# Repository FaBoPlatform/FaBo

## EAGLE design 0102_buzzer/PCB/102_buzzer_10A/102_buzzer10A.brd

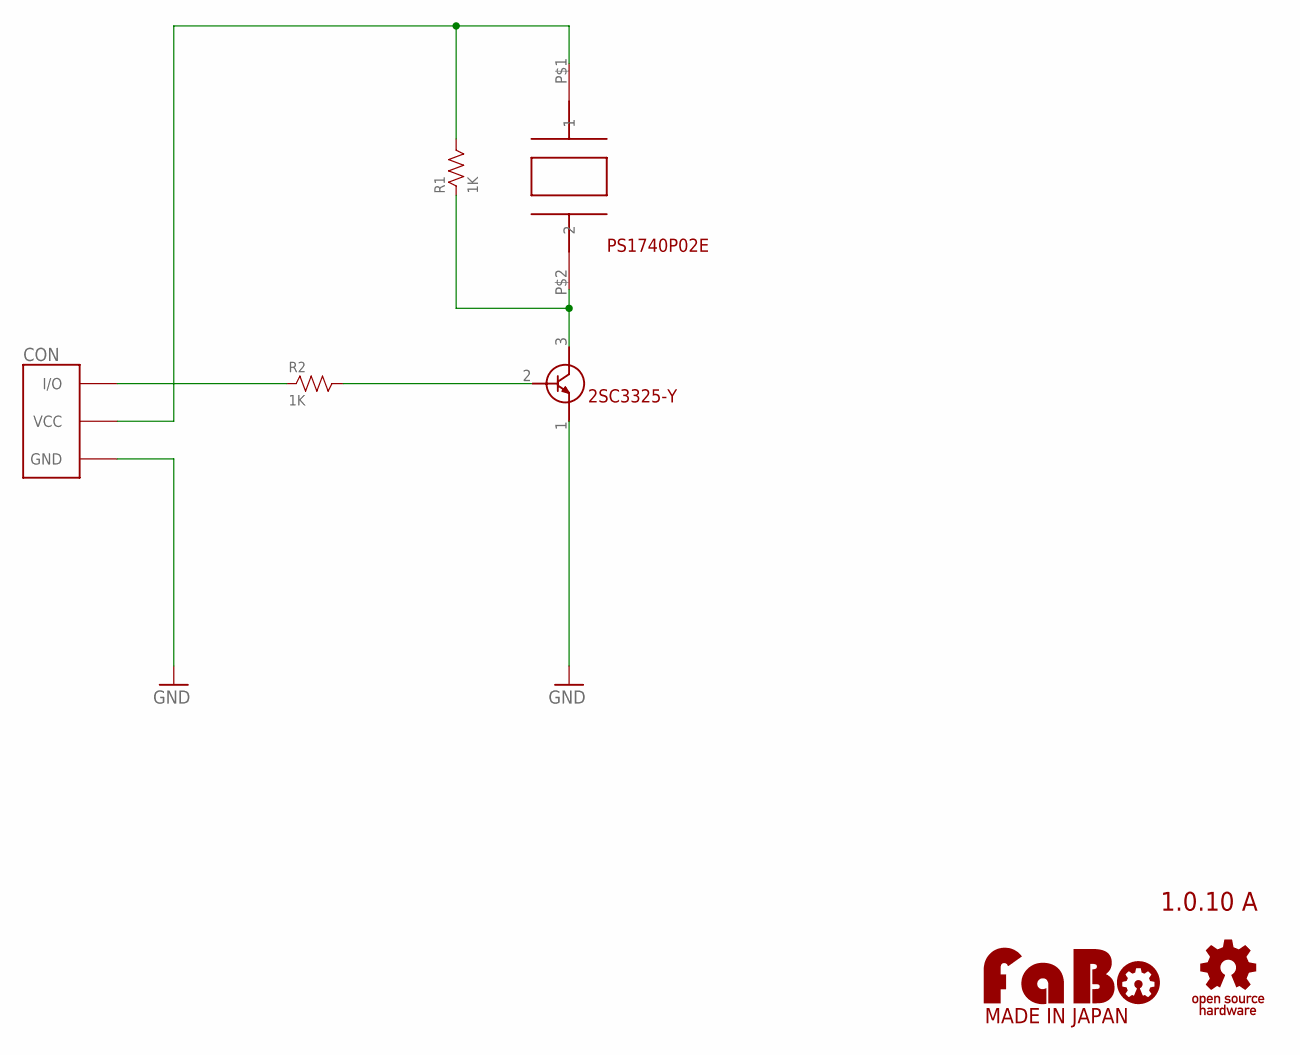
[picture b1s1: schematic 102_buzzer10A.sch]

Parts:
CON: FABO_BRICK_3PIN_INNER; FABO_BRICK_3PIN_HOLE_CON
R1, R2: 1K; 0603
T1: 2SC3325-Y; SC-59
U1: PS1740P02E
U$2: LOGO_FABO-M; LOGO_FABO_MS
U$3: LOGO_OSHW-M_BOTTOM; LOGO_OSHW_M_BOTTOM

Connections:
GND: CON.GND, T1.1 (E)
unnamed: CON.I/O, R2.1
unnamed: CON.VCC, R1.2, U1.P$1 (1)
unnamed: R1.1, T1.3 (C), U1.P$2 (2)
unnamed: R2.2, T1.2 (B)

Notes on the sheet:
1.0.10 A
PS1740P02E

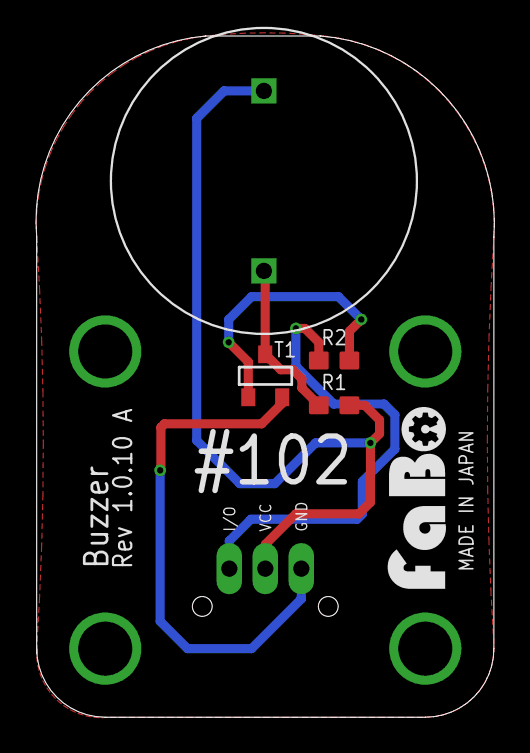
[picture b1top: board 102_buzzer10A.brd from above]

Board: 2 copper layers, 25.5 x 37.8 mm, 7 parts (0 on the bottom side), 5 nets.

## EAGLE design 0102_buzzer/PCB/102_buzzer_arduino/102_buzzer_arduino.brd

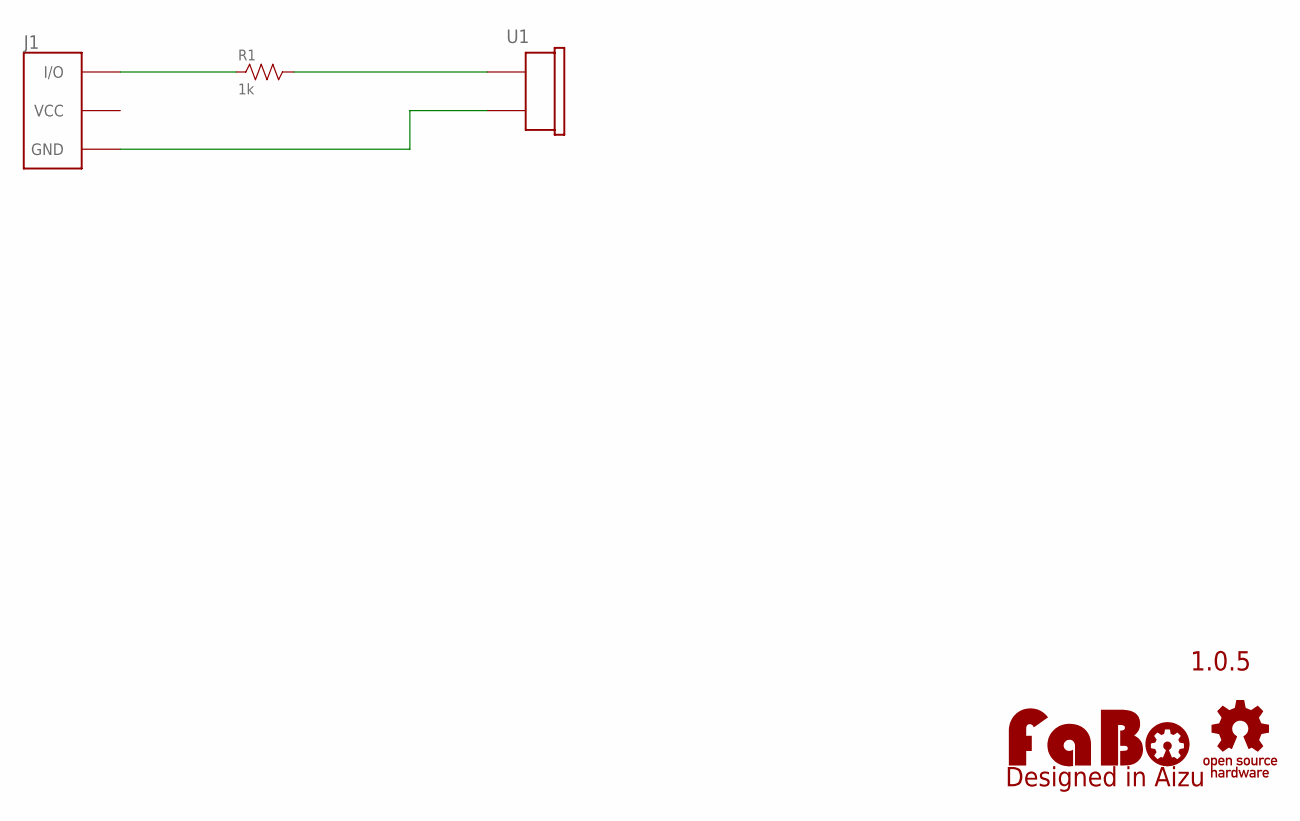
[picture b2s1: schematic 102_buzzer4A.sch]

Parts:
J1: FABO_BRICK_3PIN
LOGO1: LOGO_FABO-M; LOGO_FABO_M
R1: 1k; AXL-REGULAR
U1: BUZZER; PKM13EPYH4000-A0
U$3: LOGO_OSHW-M_BOTTOM; LOGO_OSHW_M_BOTTOM

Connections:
GND: J1.GND, U1.2
unnamed: J1.I/O, R1.1
unnamed: R1.2, U1.1

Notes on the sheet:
1.0.5

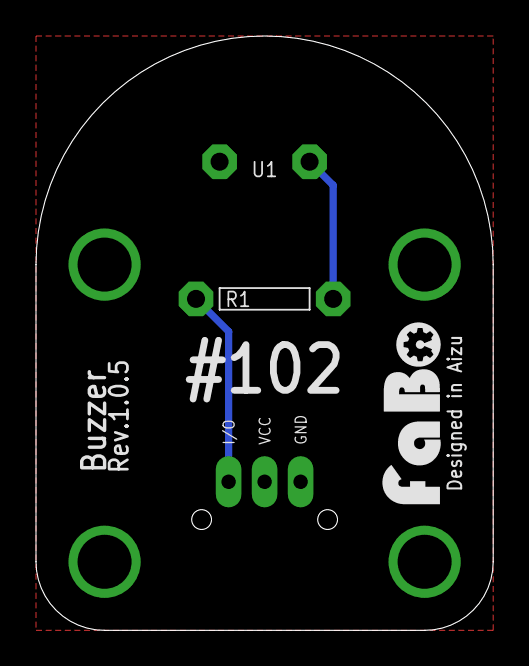
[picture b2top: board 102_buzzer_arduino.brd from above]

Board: 2 copper layers, 25.4 x 33.0 mm, 5 parts (0 on the bottom side), 3 nets.

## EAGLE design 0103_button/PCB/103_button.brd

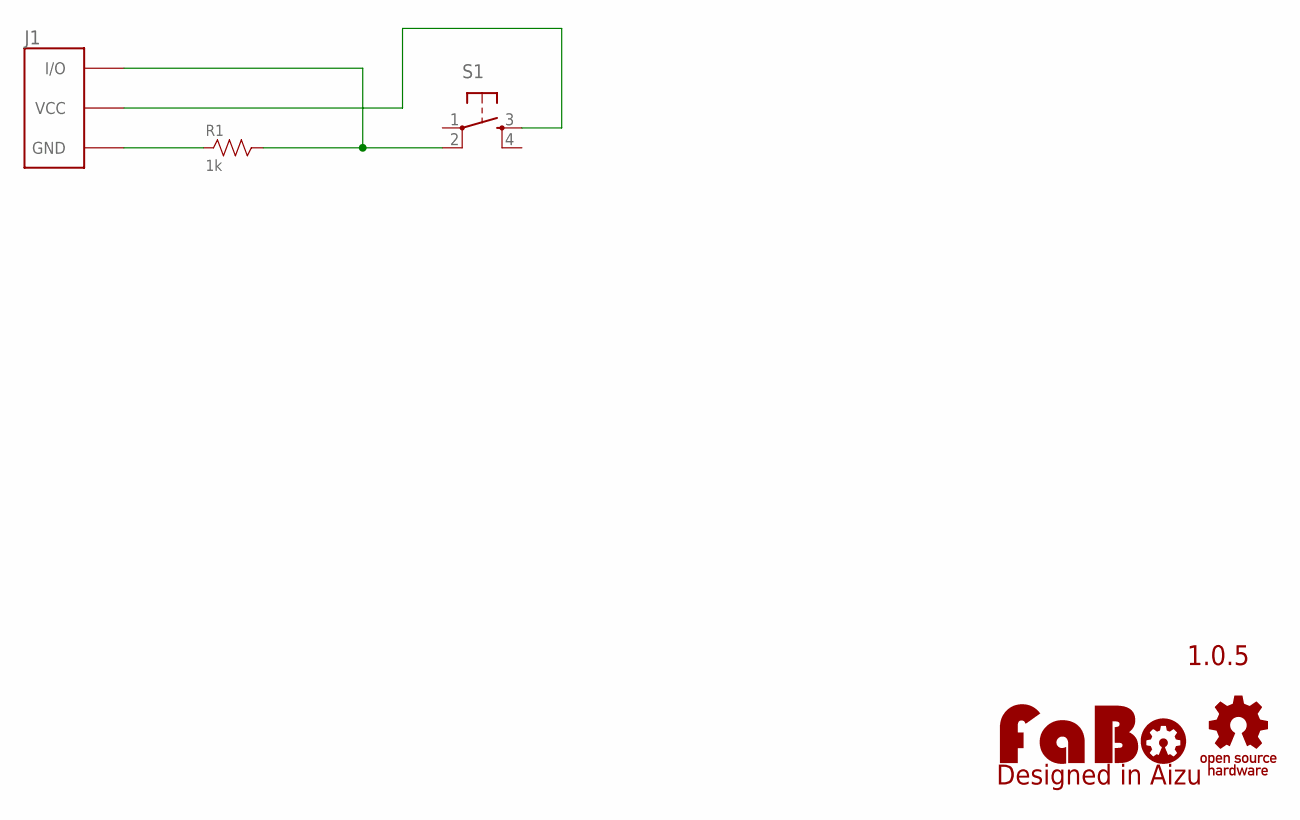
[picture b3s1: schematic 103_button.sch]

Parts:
J1: FABO_BRICK_3PIN
LOGO1: LOGO_FABO-M_BOTTOM; LOGO_FABO_M_BOTTOM
R1: 1k; AXL-REGULAR
S1: TACT-SWITCH-12MM; 1273HA-160G-G
U$2: LOGO_OSHW-M_BOTTOM; LOGO_OSHW_M_BOTTOM

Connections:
GND: J1.GND, R1.1
unnamed: J1.VCC, S1.3
unnamed: J1.I/O, R1.2, S1.2

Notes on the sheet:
1.0.5

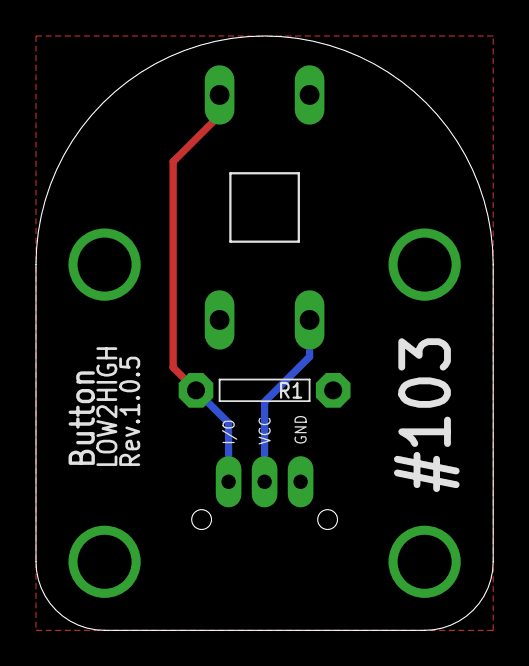
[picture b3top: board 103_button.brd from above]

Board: 2 copper layers, 25.4 x 33.0 mm, 5 parts (0 on the bottom side), 3 nets.

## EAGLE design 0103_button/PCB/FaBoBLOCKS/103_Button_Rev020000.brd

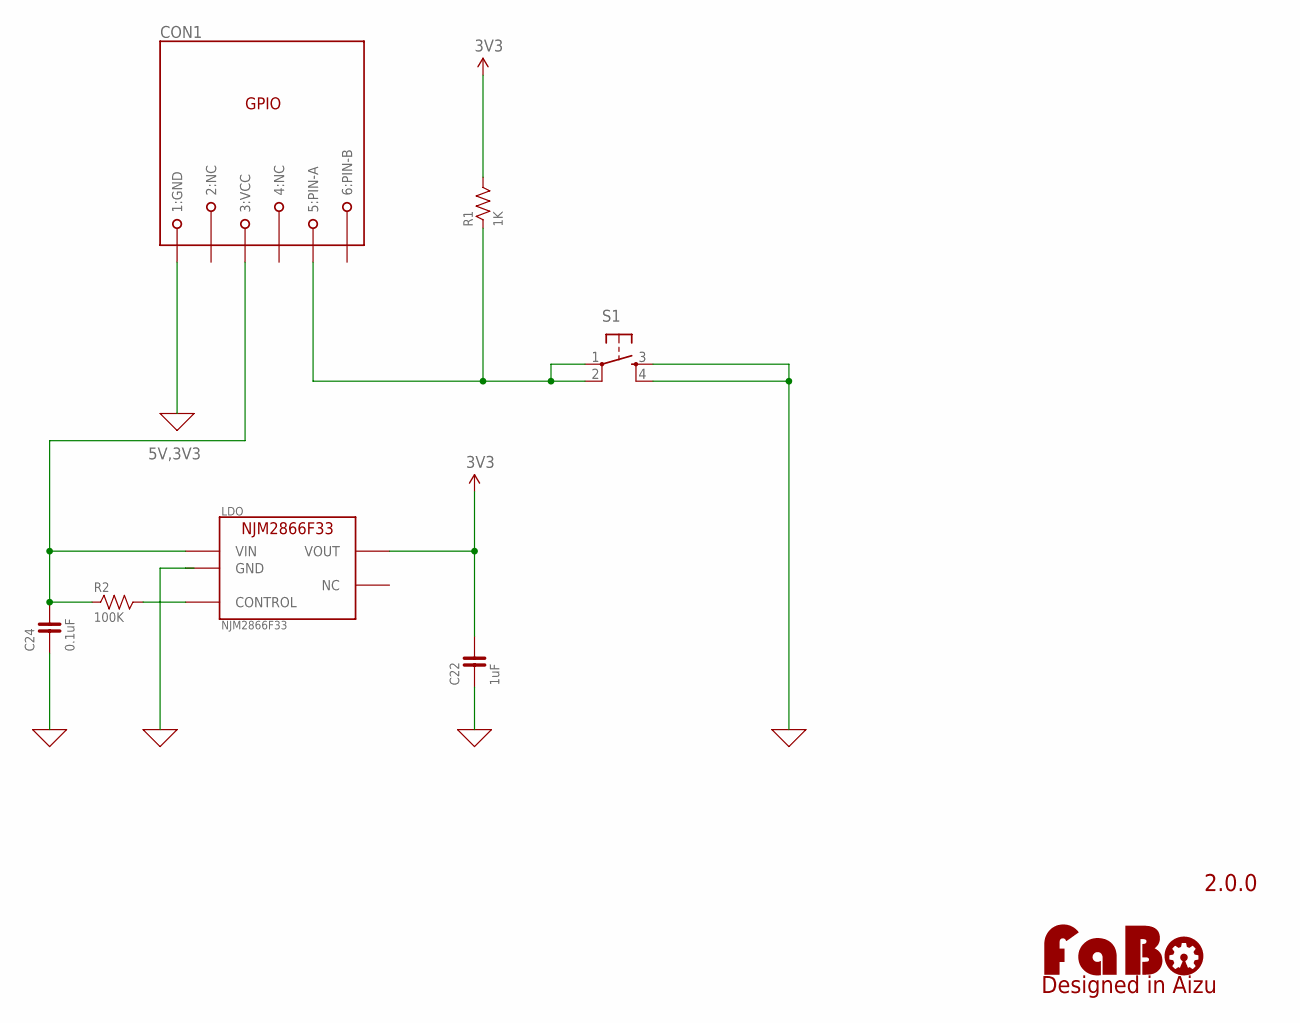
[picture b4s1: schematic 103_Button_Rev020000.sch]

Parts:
C22: 1uF; 0603
C24: 0.1uF; 0603
CON1: MODULAR-JACK-6P-RJ11_GPIO; 7002-6PXC-X
LDO: NJM2866F33; SOT-23-5
LOGO1: LOGO_FABO-M_BOTTOM; LOGO_FABO_M_BOTTOM
R1: 1K; 0603
R2: 100K; 0603
S1: TACT-SWITCH-12MM; 1273HA-160G-G

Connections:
0: C22.1, C24.1, CON1.1 (1:GND), LDO.2 (GND), S1.3, S1.4
3V3: C22.2, LDO.5 (VOUT), R1.2
5V,3V3: C24.2, CON1.3 (3:VCC), LDO.1 (VIN), R2.1
unnamed: CON1.5 (5:PIN-A), R1.1, S1.1, S1.2
unnamed: LDO.3 (CONTROL), R2.2

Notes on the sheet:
2.0.0

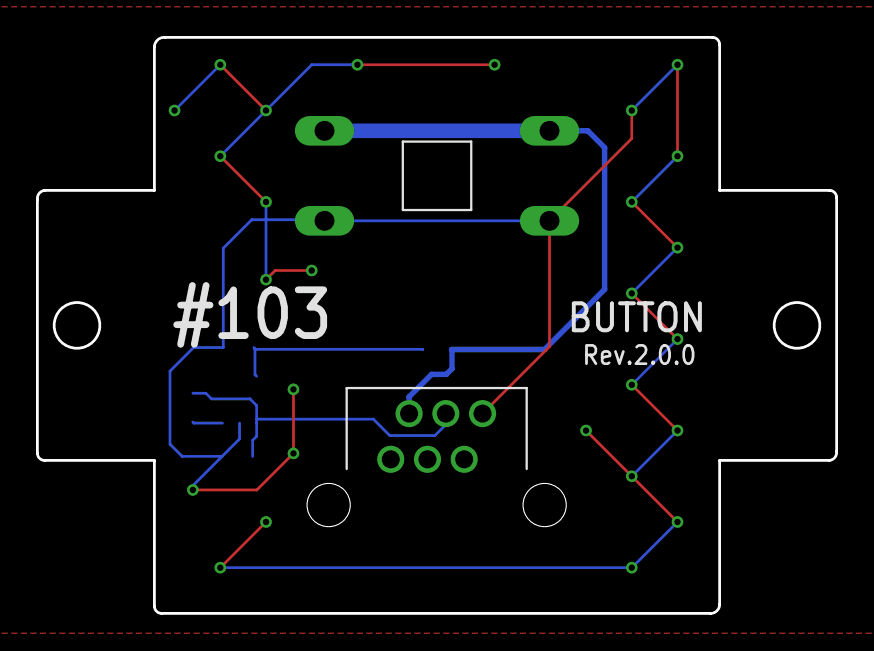
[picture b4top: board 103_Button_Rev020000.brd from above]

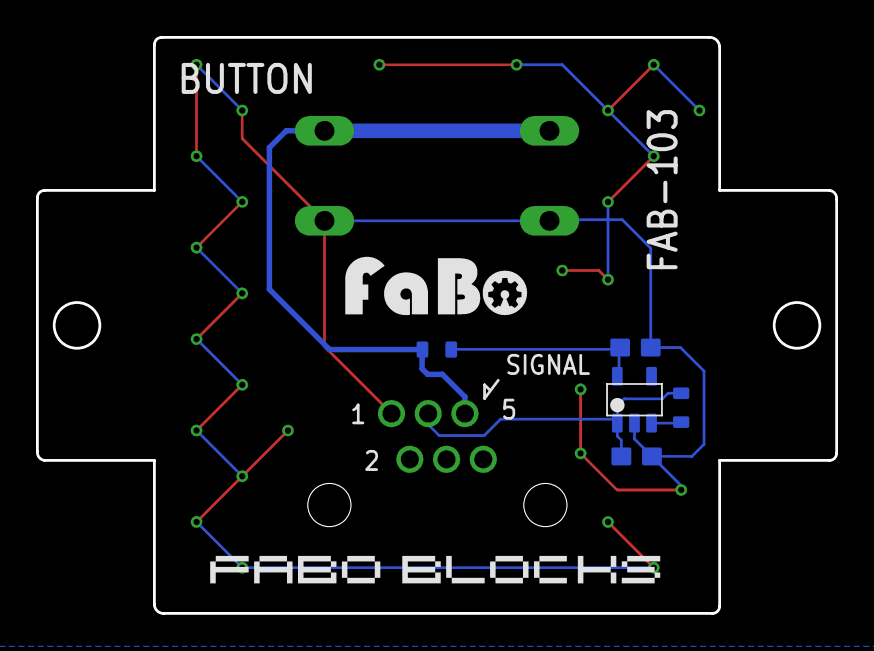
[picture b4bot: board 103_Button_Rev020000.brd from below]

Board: 2 copper layers, 44.4 x 32.0 mm, 10 parts (5 on the bottom side), 5 nets.

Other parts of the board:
U$2, U$4: 4-1BLOCK

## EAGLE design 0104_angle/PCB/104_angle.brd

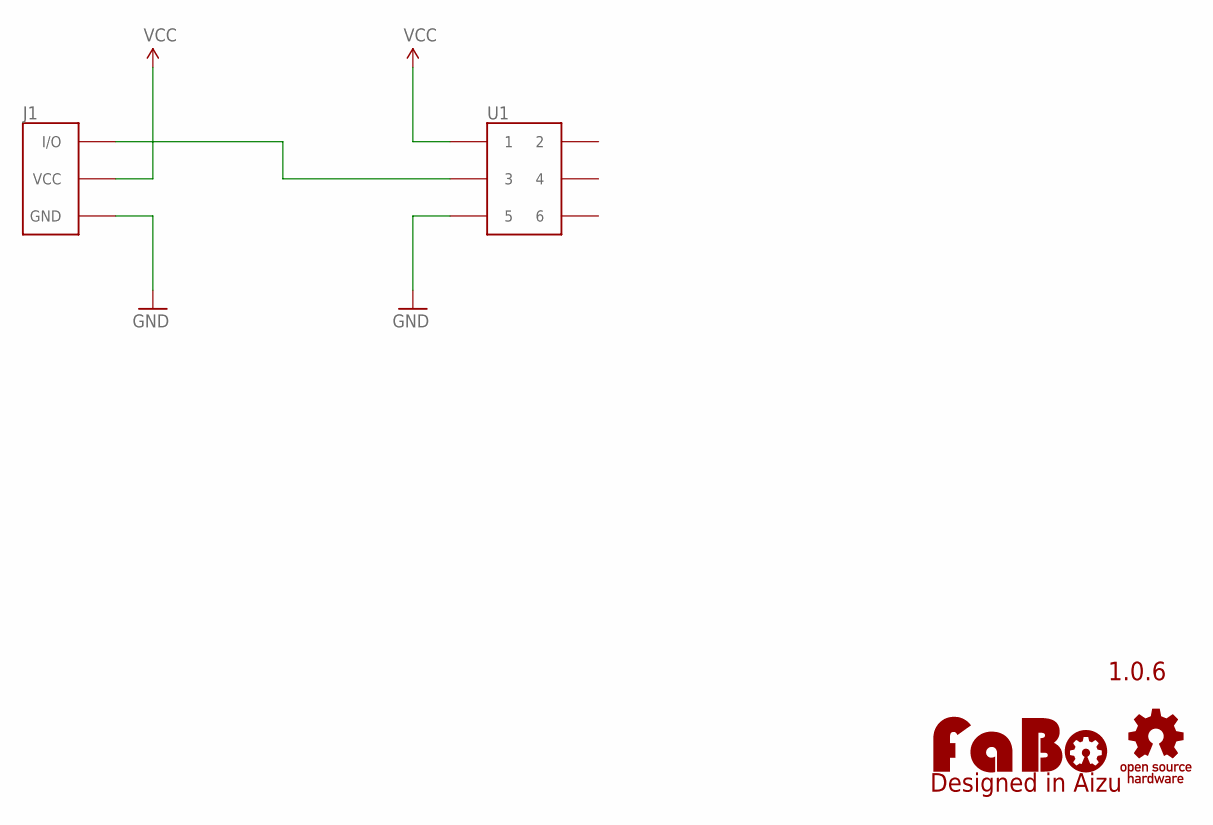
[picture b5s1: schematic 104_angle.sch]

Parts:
J1: FABO_BRICK_3PIN
LOGO1: LOGO_FABO-M; LOGO_FABO_M
U1: ROTARYENCORDER
U$3: LOGO_OSHW-M_BOTTOM; LOGO_OSHW_M_BOTTOM

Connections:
GND: J1.GND, U1.5
unnamed: J1.I/O, U1.3
VCC: J1.VCC, U1.1

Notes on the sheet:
1.0.6

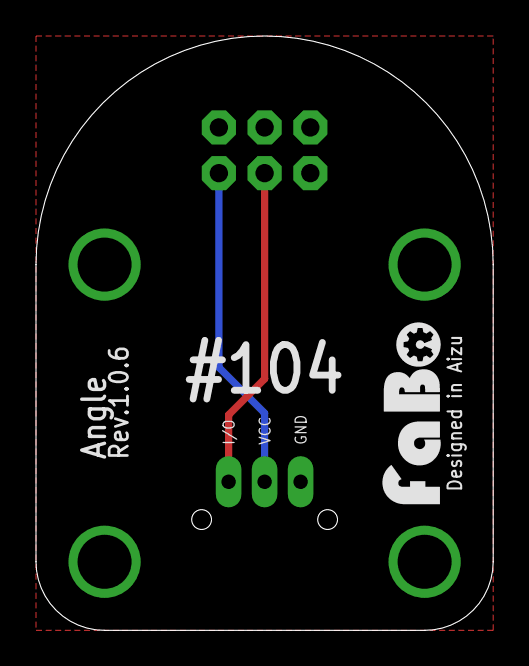
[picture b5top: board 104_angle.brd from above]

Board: 2 copper layers, 25.4 x 33.0 mm, 4 parts (0 on the bottom side), 3 nets.

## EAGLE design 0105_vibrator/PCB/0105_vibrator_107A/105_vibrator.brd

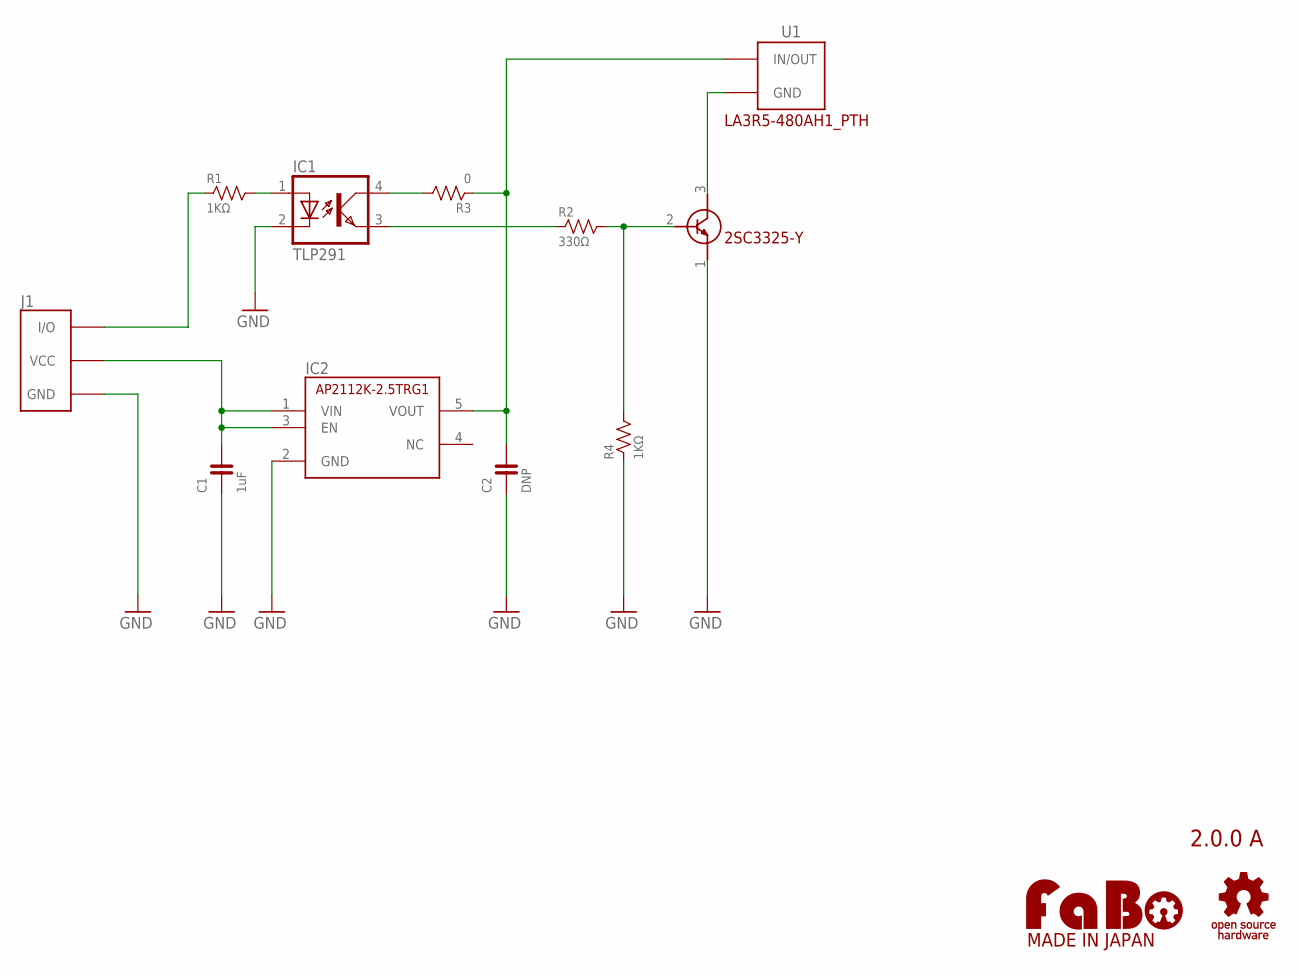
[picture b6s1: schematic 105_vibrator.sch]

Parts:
C1: 1uF; 0603
C2: DNP; 0603
IC1: TLP291; MINI-FLAT-4
IC2: AP2112-2.5; SOT-23-5
J1: FABO_BRICK_3PIN
R1, R4: 1KΩ; 0603
R2: 330Ω; 0603
R3: 0; 0603
TR1: 2SC3325-Y; SC-59
U1: VIBRATOR; LA3R5-480AH1_PTH
U$2: LOGO_OSHW-M_BOTTOM; LOGO_OSHW_M_BOTTOM
U$3: LOGO_FABO-M; LOGO_FABO_MS

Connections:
GND: C1.1, C2.1, IC1.2 (C), IC2.2 (GND), J1.GND, R4.1, TR1.1 (E)
unnamed: J1.I/O, R1.1
unnamed: IC1.1 (A), R1.2
unnamed: C1.2, IC2.1 (VIN), IC2.3 (EN), J1.VCC
unnamed: IC1.3 (EMIT), R2.1
unnamed: C2.2, IC2.5 (VOUT), R3.1, U1.P$1 (IN/OUT)
unnamed: IC1.4 (COL), R3.2
unnamed: TR1.3 (C), U1.P$2 (GND)
unnamed: R2.2, R4.2, TR1.2 (B)

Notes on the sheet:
2.0.0 A
LA3R5-480AH1_PTH

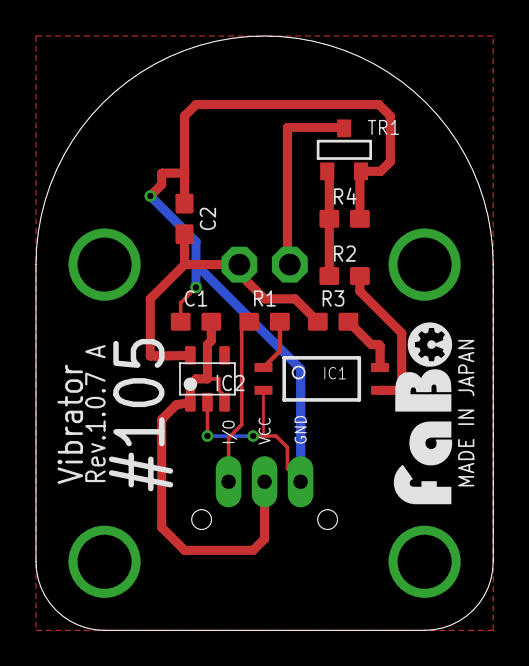
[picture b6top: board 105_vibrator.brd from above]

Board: 2 copper layers, 25.4 x 33.0 mm, 13 parts (0 on the bottom side), 9 nets.

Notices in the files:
parts and their libraries:
FaBo-etc: Released under the Creative Commons Attribution-ShareAlike 4.0 License
https://creativecommons.org/licenses/by-sa/4.0
FaBo-etc: Released under the Creative Commons
